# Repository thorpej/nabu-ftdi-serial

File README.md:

# nabu-ftdi-serial
A serial interposer board for NABU PCs with a FTDI USB-serial adapter and
hardware flow control

This is a simple serial interposer board for NABU PCs that intercepts
the Tx and Rx signals from the TR1863 UART and routes them to an FTDI
USB-serial adapter rather than to the RS422 line drivers on the NABU
main board.

In addition to intercepting the Tx and Rx signals, it also provides two
enhancements:

* The option to use a 1.8432MHz oscillator to generate a 115.2K baud
  rate on the UART, rather than the stock 111.8K baud that the NABU's
  clock generates.  Two different oscillator footprints are provided,
  for your convenience.  A jumper is provided to select the clock source.

* The option to enable hardware flow control.  This is done by connecting
  the TR1863's _DR_ signal (Data Received) to the _CTS_ input on the FTDI.
  Because _DR_ is active-high and _CTS_ is active-low, a pending receive
  interrupt effectively de-asserts _CTS_, which will cause the sender to
  pause transmitting until the interrupt has been serviced.

To build this board you're oging to need an FTDI USB -> serial interface
chip mounted on some sort of break-out board.  The board provides 2
footprints to provide some flexibility.

The first footprint is for a 6-pin right-angle pin header that is meant
for an Adafruit 6-pin female FTDI connector.  Such a connector can be
found on the [Adafruit FTDI Friend](https://www.adafruit.com/product/284),
the [Adafruit FTDI Serial TTL-232 Cable](https://www.adafruit.com/product/70),
or the [Adafruit FTDI Serial TTL-232 USB Type C 5V Cable](https://www.adafruit.com/product/4364).
There are other cables out there with a compatible 6-pin connector,
but I specifically referenced the pin configuration of the Adafruit
products.

The other option is one of the FTDI FT232RL boards that are all over
Ali Express.  I ordered [this one](https://www.aliexpress.us/item/2251832463833524.html),
but there are lots of identical boards floating around.

This board is 99.9% the work of Kris Sekula (MyGeekyHobby.com).  All I did
was add the hardware flow control modification.  Kudos to Kris for publishing
his idea [here](https://github.com/Kris-Sekula/NABU/tree/main/RS422Alternative).

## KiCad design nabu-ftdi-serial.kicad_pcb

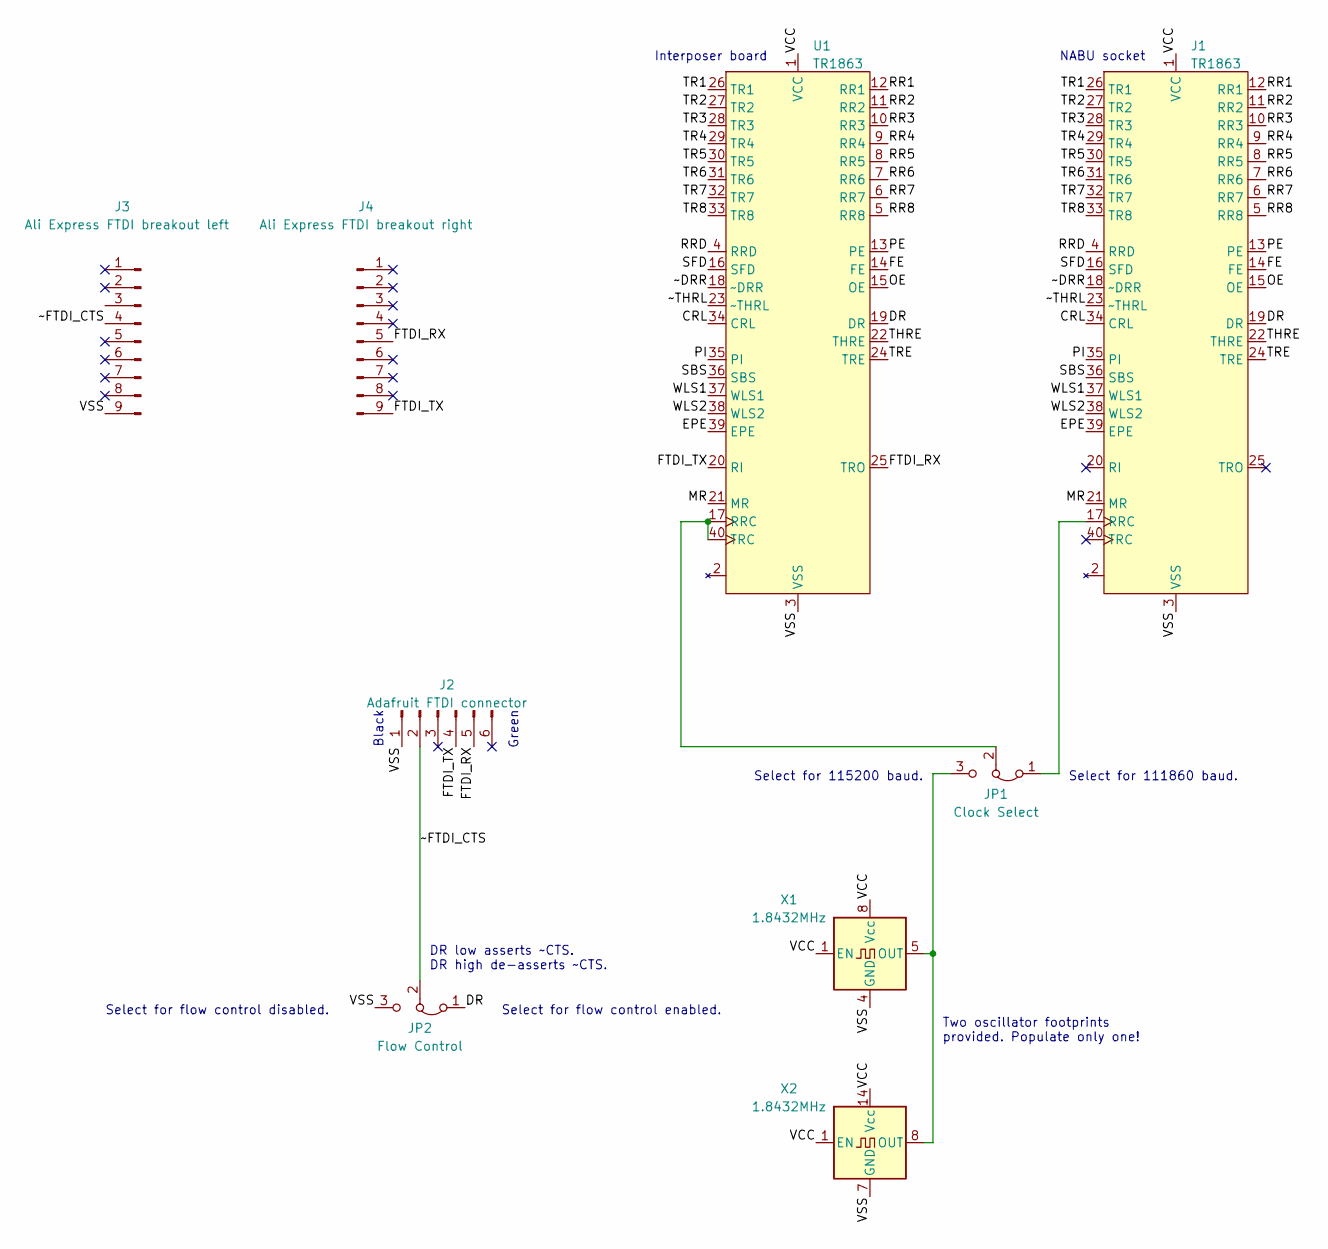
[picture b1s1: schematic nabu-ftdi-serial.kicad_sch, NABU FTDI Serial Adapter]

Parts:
J1: TR1863; DIP-40_W15.24mm
J2: Adafruit FTDI connector; PinHeader_1x06_P2.54mm_Horizontal
J3: Ali Express FTDI breakout left; PinHeader_1x09_P2.54mm_Vertical
J4: Ali Express FTDI breakout right; PinHeader_1x09_P2.54mm_Vertical
JP1: Clock Select; PinHeader_1x03_P2.54mm_Vertical
JP2: Flow Control; PinHeader_1x03_P2.54mm_Vertical
U1: TR1863; DIP-40_W15.24mm_Socket
X1: 1.8432MHz; Oscillator_DIP-8
X2: 1.8432MHz; Oscillator_DIP-14

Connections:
/CRL: J1.34 (CRL), U1.34 (CRL)
/DR: J1.19 (DR), JP2.1 (A), U1.19 (DR)
/EPE: J1.39 (EPE), U1.39 (EPE)
/FE: J1.14 (FE), U1.14 (FE)
/FTDI_RX: J2.5, J4.5, U1.25 (TRO)
/FTDI_TX: J2.4, J4.9, U1.20 (RI)
/MR: J1.21 (MR), U1.21 (MR)
/OE: J1.15 (OE), U1.15 (OE)
/PE: J1.13 (PE), U1.13 (PE)
/PI: J1.35 (PI), U1.35 (PI)
/RR1: J1.12 (RR1), U1.12 (RR1)
/RR2: J1.11 (RR2), U1.11 (RR2)
/RR3: J1.10 (RR3), U1.10 (RR3)
/RR4: J1.9 (RR4), U1.9 (RR4)
/RR5: J1.8 (RR5), U1.8 (RR5)
/RR6: J1.7 (RR6), U1.7 (RR6)
/RR7: J1.6 (RR7), U1.6 (RR7)
/RR8: J1.5 (RR8), U1.5 (RR8)
/RRD: J1.4 (RRD), U1.4 (RRD)
/SBS: J1.36 (SBS), U1.36 (SBS)
/SFD: J1.16 (SFD), U1.16 (SFD)
/THRE: J1.22 (THRE), U1.22 (THRE)
/TR1: J1.26 (TR1), U1.26 (TR1)
/TR2: J1.27 (TR2), U1.27 (TR2)
/TR3: J1.28 (TR3), U1.28 (TR3)
/TR4: J1.29 (TR4), U1.29 (TR4)
/TR5: J1.30 (TR5), U1.30 (TR5)
/TR6: J1.31 (TR6), U1.31 (TR6)
/TR7: J1.32 (TR7), U1.32 (TR7)
/TR8: J1.33 (TR8), U1.33 (TR8)
/TRE: J1.24 (TRE), U1.24 (TRE)
/VCC: J1.1 (VCC), U1.1 (VCC), X1.1 (EN), X1.8 (Vcc), X2.1 (EN), X2.14 (Vcc)
/VSS: J1.3 (VSS), J2.1, J3.9, JP2.3 (B), U1.3 (VSS), X1.4 (GND), X2.7 (GND)
/WLS1: J1.37 (WLS1), U1.37 (WLS1)
/WLS2: J1.38 (WLS2), U1.38 (WLS2)
/~DRR: J1.18 (~DRR), U1.18 (~DRR)
/~FTDI_CTS: J2.2, J3.4, JP2.2 (C)
/~THRL: J1.23 (~THRL), U1.23 (~THRL)
unnamed: J1.17 (RRC), JP1.1 (A)
unnamed: JP1.3 (B), X1.5 (OUT), X2.8 (OUT)
unnamed: JP1.2 (C), U1.17 (RRC), U1.40 (TRC)

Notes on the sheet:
Green
Select for flow control disabled.
Select for flow control enabled.
NABU socket
Interposer board
Two oscillator footprints provided. Populate only one!
Select for 111860 baud.
Black
DR low asserts ~CTS. DR high de-asserts ~CTS.
Select for 115200 baud.

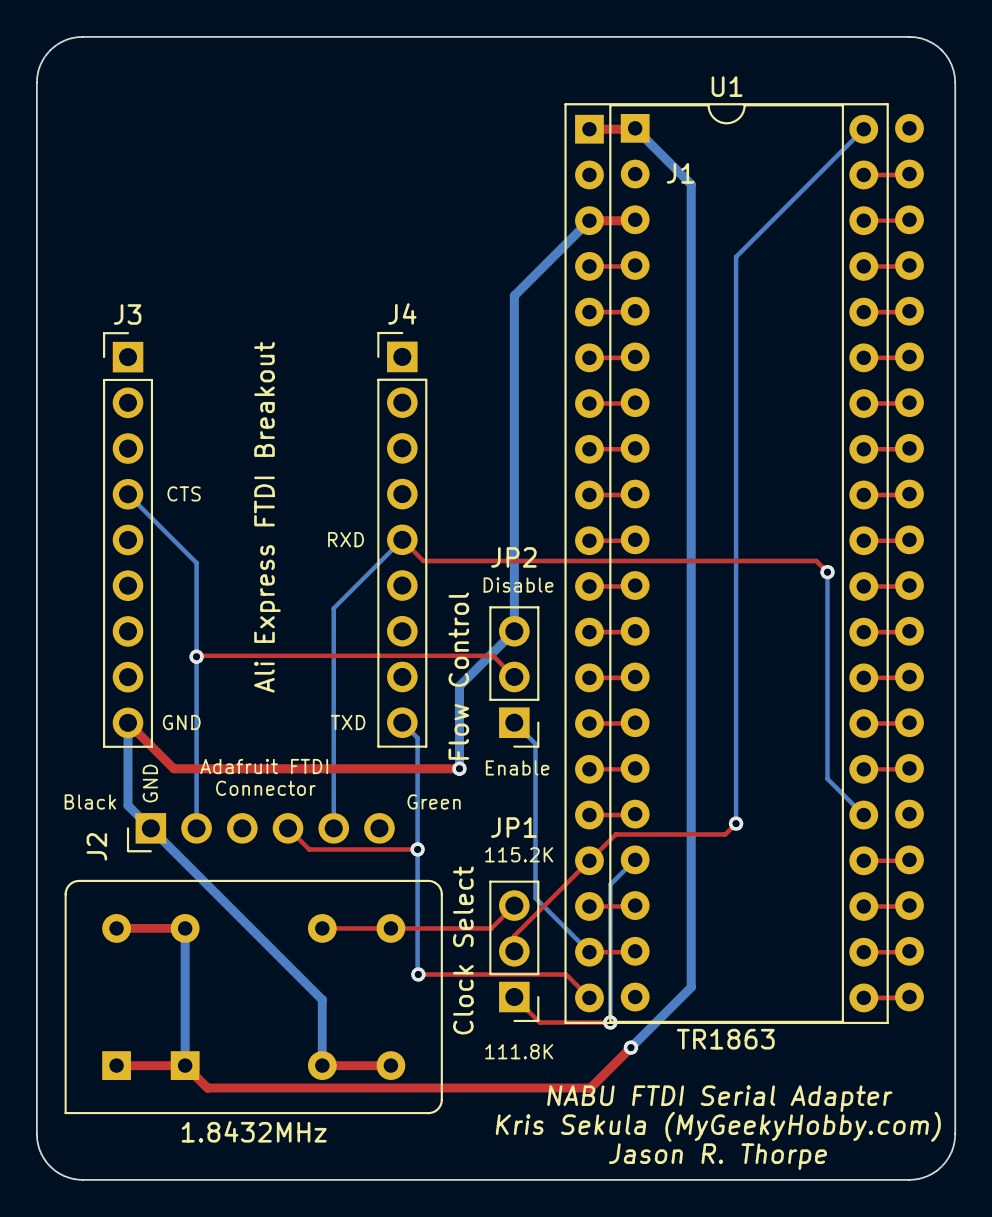
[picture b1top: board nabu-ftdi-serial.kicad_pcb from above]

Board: 2 copper layers, 51.0 x 63.5 mm, 9 parts (0 on the bottom side), 41 nets.

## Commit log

2023-02-12 Add design files for the FDTI serial interposer board.
2023-02-12 Describe what's going on here.
2023-02-12 Fix typo.
2023-02-13 Add Gerbers for 1.0.
2023-02-13 Add easily-viewable images of the schematic and PCB.
2023-02-14 Add a reference to the serial board options.
2023-02-14 Markdown botch.
